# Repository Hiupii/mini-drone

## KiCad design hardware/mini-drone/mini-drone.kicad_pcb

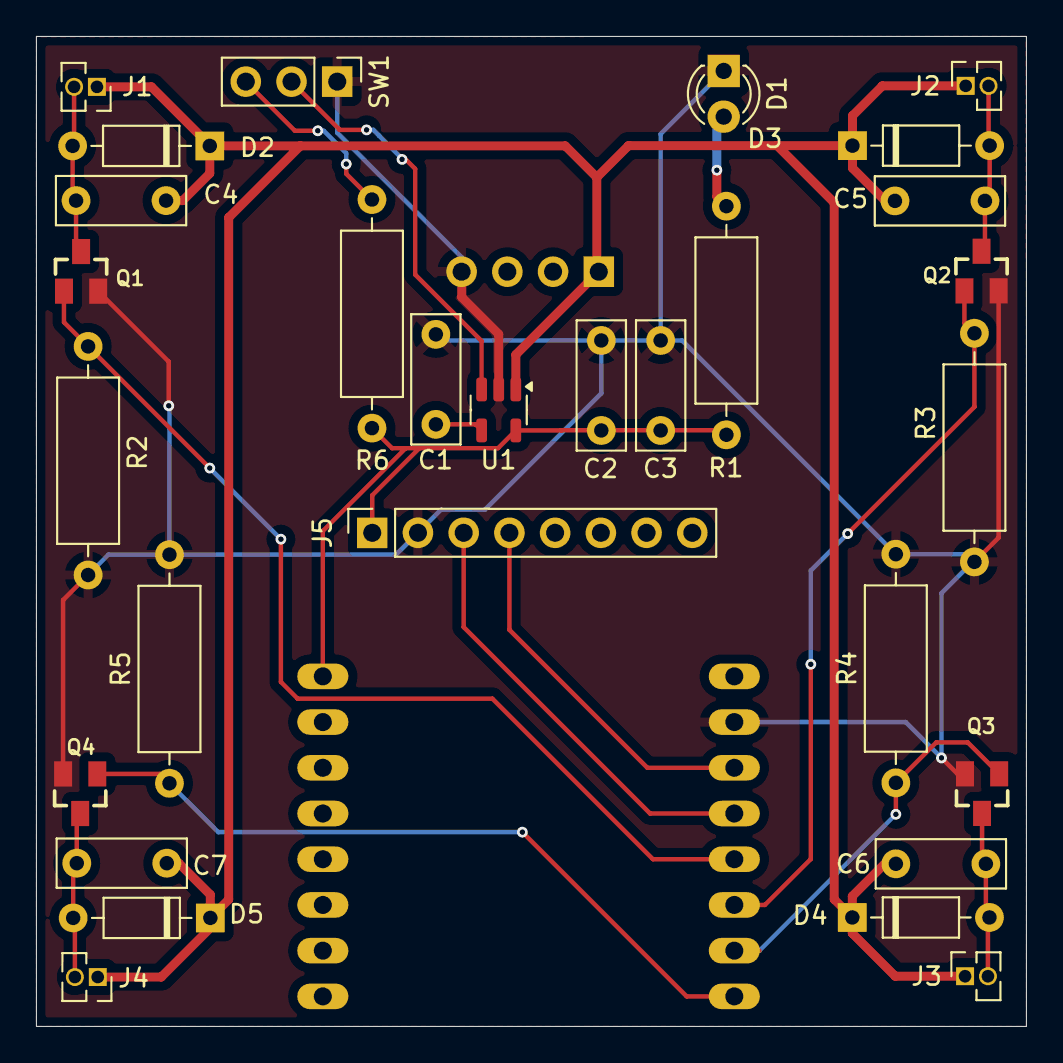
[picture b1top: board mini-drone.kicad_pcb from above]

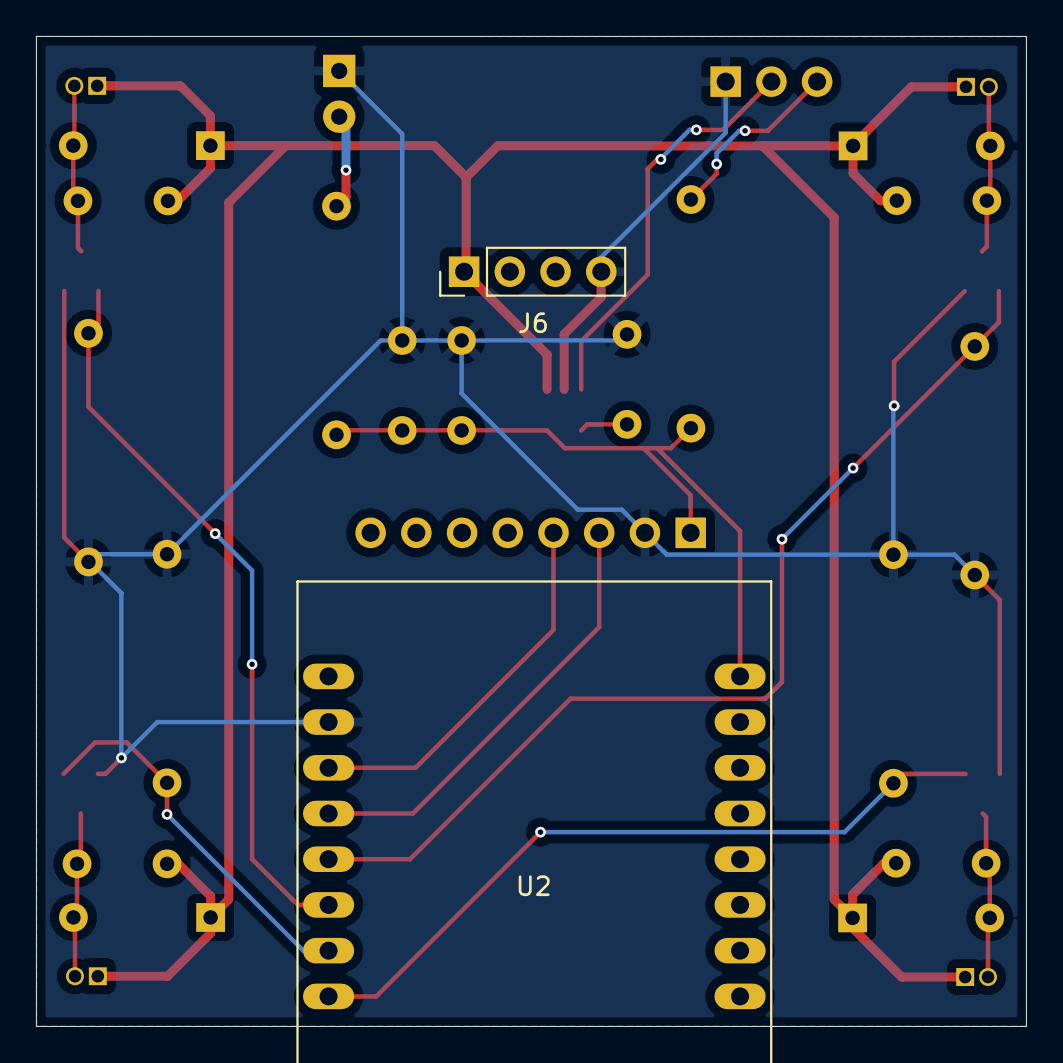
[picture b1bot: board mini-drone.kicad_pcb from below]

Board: 2 copper layers, 55.0 x 55.0 mm, 31 parts (2 on the bottom side), 17 nets.

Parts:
C1: 470pF; C_Disc_D7.0mm_W2.5mm_P5.00mm
C2: 2.2uF; C_Disc_D7.0mm_W2.5mm_P5.00mm
C3: 10uF; C_Disc_D7.0mm_W2.5mm_P5.00mm
C4, C5, C6, C7: 1uF; C_Disc_D7.0mm_W2.5mm_P5.00mm
D1: LED; LED_D3.0mm
D2, D3, D4, D5: 1N4148; D_DO-35_SOD27_P7.62mm_Horizontal
J1, J2, J3, J4: Conn_01x02_Socket; PinSocket_1x02_P1.27mm_Vertical
J5: Conn_01x08_Socket; PinSocket_1x08_P2.54mm_Vertical
J6: Conn_01x04_Pin; PinHeader_1x04_P2.54mm_Vertical
Q1, Q2, Q3, Q4: SI2302; SOT23
R1: 470R; R_Axial_DIN0309_L9.0mm_D3.2mm_P12.70mm_Horizontal
R2, R3, R4, R5: 10k; R_Axial_DIN0309_L9.0mm_D3.2mm_P12.70mm_Horizontal
R6: 100K; R_Axial_DIN0309_L9.0mm_D3.2mm_P12.70mm_Horizontal
SW1: K3-1280S-F1; PinHeader_1x03_P2.54mm_Vertical
U1: MIC5219-3.3YM5; SOT-23-5
U2: ESP32-CAM

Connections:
+3.3V: C2.1, C3.1, J5.1, R1.1, R6.1, U1.5 (OUT), U2.P$16 (3V3)
/+OUT: C4.1, C5.1, C6.1, C7.1, D2.1 (K), D3.1 (K), D4.1 (K), D5.1 (K), J1.1, J2.1, J3.1, J4.1, J6.1, U1.1 (IN)
/LDO_H: R6.2, SW1.3 (C)
/MOT_1: Q1.1, R2.1, U2.P$5 (IO15)
/MOT_2: Q2.1, R3.1, U2.P$6 (IO14)
/MOT_3: Q3.1, R4.1, U2.P$7 (IO2)
/MOT_4: Q4.1, R5.1, U2.P$8 (IO4)
/MPU_SCL: J5.3, U2.P$4 (IO13)
/MPU_SDA: J5.4, U2.P$3 (IO12)
GND: C1.2, C2.2, C3.2, D1.1 (K), J5.2, J6.4, Q1.2, Q2.2, Q3.2, Q4.2, R2.2, R3.2, R4.2, R5.2, SW1.1 (A), U1.2 (GND), U2.P$2 (GND)
LDO_EN: SW1.2 (B), U1.3 (EN)
unnamed: D1.2 (A), R1.2
unnamed: C4.2, D2.2 (A), J1.2, Q1.3
unnamed: C5.2, D3.2 (A), J2.2, Q2.3
unnamed: C6.2, D4.2 (A), J3.2, Q3.3
unnamed: C7.2, D5.2 (A), J4.2, Q4.3
unnamed: C1.1, U1.4 (BP)

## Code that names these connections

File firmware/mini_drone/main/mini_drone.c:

#include <stdio.h>
#include "freertos/FreeRTOS.h"
#include "freertos/task.h"
#include "esp_log.h"
#include "esp_event.h"
#include "esp_system.h"
#include "PID.h"
#include "mpu6050.h"
#include "driver/ledc.h"
#include "math.h"

/*----------mpu6050 var----------*/
#define MPU_ADDR (0x68)

#define CONFIG_SDA_GPIO GPIO_NUM_13
#define CONFIG_SCL_GPIO GPIO_NUM_12

static const char *MPU_TAG = "mpu6050_log";

static mpu6050_acceleration_t accel = { 0 };
static mpu6050_rotation_t rotation = { 0 };

static float input_pitch = 0.0f;
static float input_roll = 0.0f;
static float g = 9.81f;

/*----------pid var----------*/

struct pid_controller pitch_control;
pid_t pitch_pid;

struct pid_controller roll_control;
pid_t roll_pid;

float Kp = 3.55;   // Proportional param
float Ki = 0.005;   // Integral param
float Kd = 2.05;   // Derivative param

static float output_pitch = 0.0f;
static float output_roll = 0.0f;
static float setpoint_pitch = 0.0f;
static float setpoint_roll = 0.0f;


/*----------motor var----------*/
#define MOT_1 GPIO_NUM_14
#define MOT_2 GPIO_NUM_15
#define MOT_3 GPIO_NUM_2
#define MOT_4 GPIO_NUM_4

int base_throttle = 4915;
int motor1_pwm = 0;
int motor2_pwm = 0;
int motor3_pwm = 0;
int motor4_pwm = 0;

int constrain(int value, int min_value, int max_value);

void mpu6050_task(void *pvParameters)
{
    mpu6050_dev_t dev = { 0 };

    ESP_ERROR_CHECK(mpu6050_init_desc(&dev, MPU_ADDR, 0, CONFIG_SDA_GPIO, CONFIG_SCL_GPIO));

    while (1)
    {
        esp_err_t res = i2c_dev_probe(&dev.i2c_dev, I2C_DEV_WRITE);
        if (res == ESP_OK)
        {
            ESP_LOGI(MPU_TAG, "Found MPU60x0 device");
            break;
        }
        ESP_LOGE(MPU_TAG, "MPU60x0 not found");
        vTaskDelay(pdMS_TO_TICKS(1000));
    }

    ESP_ERROR_CHECK(mpu6050_init(&dev));

    ESP_LOGI(MPU_TAG, "Accel range: %d", dev.ranges.accel);
    ESP_LOGI(MPU_TAG, "Gyro range:  %d", dev.ranges.gyro);

    while (1)
    {
        ESP_ERROR_CHECK(mpu6050_get_motion(&dev, &accel, &rotation));
        input_pitch = asinf(accel.x * g / g) * 180 / M_PI;
        input_roll = atan2(accel.y, accel.z) * 180 / M_PI;
        ESP_LOGI(MPU_TAG, "Pitch: %f", input_pitch);
        ESP_LOGI(MPU_TAG, "Roll : %f", input_roll);

        pid_compute(pitch_pid);
        pid_compute(roll_pid);

        // ESP_LOGI(PID_TAG, "Input Pitch: %f, Output Pitch: %f", input_pitch, output_pitch);
        // ESP_LOGI(PID_TAG, "Input Roll : %f, Output Roll : %f", input_roll, output_roll);

        motor1_pwm = base_throttle + output_pitch - output_roll;
        motor2_pwm = base_throttle + output_pitch + output_roll;
        motor3_pwm = base_throttle - output_pitch + output_roll;
        motor4_pwm = base_throttle - output_pitch - output_roll;

        motor1_pwm = constrain(motor1_pwm, 0, 8191);  // 13-bit PWM max value is 8191
        motor2_pwm = constrain(motor2_pwm, 0, 8191);
        motor3_pwm = constrain(motor3_pwm, 0, 8191);
        motor4_pwm = constrain(motor4_pwm, 0, 8191);

        // ESP_LOGI(PID_TAG, "mot1_pwm: %d", motor1_pwm-base_throttle);
        // ESP_LOGI(PID_TAG, "mot2_pwm: %d", motor2_pwm-base_throttle);
        // ESP_LOGI(PID_TAG, "mot3_pwm: %d", motor3_pwm-base_throttle);
        // ESP_LOGI(PID_TAG, "mot4_pwm: %d", motor4_pwm-base_throttle);

        ledc_set_duty(LEDC_HIGH_SPEED_MODE, LEDC_CHANNEL_0, motor1_pwm);
        ledc_set_duty(LEDC_HIGH_SPEED_MODE, LEDC_CHANNEL_1, motor2_pwm);
        ledc_set_duty(LEDC_HIGH_SPEED_MODE, LEDC_CHANNEL_2, motor3_pwm);
        ledc_set_duty(LEDC_HIGH_SPEED_MODE, LEDC_CHANNEL_3, motor4_pwm);
        ledc_update_duty(LEDC_HIGH_SPEED_MODE, LEDC_CHANNEL_0);
        ledc_update_duty(LEDC_HIGH_SPEED_MODE, LEDC_CHANNEL_1);
        ledc_update_duty(LEDC_HIGH_SPEED_MODE, LEDC_CHANNEL_2);
        ledc_update_duty(LEDC_HIGH_SPEED_MODE, LEDC_CHANNEL_3);

        vTaskDelay(pdMS_TO_TICKS(100));
    }
}

// Thiết lập PWM cho động cơ
void setup_pwm() {
    // Cấu hình PWM cho 4 động cơ
    ledc_timer_config_t ledc_timer = {
        .duty_resolution = LEDC_TIMER_13_BIT, // Độ phân giải PWM
        .freq_hz = 5000,                      // Tần số PWM
        .speed_mode = LEDC_HIGH_SPEED_MODE,   // Chế độ tốc độ cao
        .timer_num = LEDC_TIMER_0             // Sử dụng bộ timer 0
    };
    ledc_timer_config(&ledc_timer);

    ledc_channel_config_t ledc_channel[4] = {
        {.channel    = LEDC_CHANNEL_0,
         .duty       = 0,
         .gpio_num   = MOT_1,          // Chân GPIO nối với động cơ 1
         .speed_mode = LEDC_HIGH_SPEED_MODE,
         .hpoint     = 0,
         .timer_sel  = LEDC_TIMER_0},

        {.channel    = LEDC_CHANNEL_1,
         .duty       = 0,
         .gpio_num   = MOT_2,          // Chân GPIO nối với động cơ 2
         .speed_mode = LEDC_HIGH_SPEED_MODE,
         .hpoint     = 0,
         .timer_sel  = LEDC_TIMER_0},

        {.channel    = LEDC_CHANNEL_2,
         .duty       = 0,
         .gpio_num   = MOT_3,          // Chân GPIO nối với động cơ 3
         .speed_mode = LEDC_HIGH_SPEED_MODE,
         .hpoint     = 0,
         .timer_sel  = LEDC_TIMER_0},

        {.channel    = LEDC_CHANNEL_3,
         .duty       = 0,
         .gpio_num   = MOT_4,          // Chân GPIO nối với động cơ 4
         .speed_mode = LEDC_HIGH_SPEED_MODE,
         .hpoint     = 0,
         .timer_sel  = LEDC_TIMER_0},
    };
    for (int i = 0; i < 4; i++) {
        ledc_channel_config(&ledc_channel[i]);
    }
}

void app_main()
{
    setup_pwm();

    ledc_set_duty(LEDC_HIGH_SPEED_MODE, LEDC_CHANNEL_0, base_throttle);
    ledc_set_duty(LEDC_HIGH_SPEED_MODE, LEDC_CHANNEL_1, base_throttle);
    ledc_set_duty(LEDC_HIGH_SPEED_MODE, LEDC_CHANNEL_2, base_throttle);
    ledc_set_duty(LEDC_HIGH_SPEED_MODE, LEDC_CHANNEL_3, base_throttle);
    ledc_update_duty(LEDC_HIGH_SPEED_MODE, LEDC_CHANNEL_0);
    ledc_update_duty(LEDC_HIGH_SPEED_MODE, LEDC_CHANNEL_1);
    ledc_update_duty(LEDC_HIGH_SPEED_MODE, LEDC_CHANNEL_2);
    ledc_update_duty(LEDC_HIGH_SPEED_MODE, LEDC_CHANNEL_3);

    // task
    ESP_ERROR_CHECK(i2cdev_init());

    pitch_pid = pid_create(&pitch_control, &input_pitch, &output_pitch, &setpoint_pitch, Kd, Ki, Kp);
    roll_pid = pid_create(&roll_control, &input_roll, &output_roll, &setpoint_roll, Kp, Ki, Kd);

    pid_limits(pitch_pid, -8191, 8191);
    pid_limits(roll_pid, -8191, 8191);

    pid_auto(pitch_pid);
    pid_auto(roll_pid);

    xTaskCreate(mpu6050_task, "mpu6050_test", configMINIMAL_STACK_SIZE * 6, NULL, 5, NULL);
}

int constrain(int value, int min_value, int max_value) {
    if (value < min_value) {
        return min_value;
    } else if (value > max_value) {
        return max_value;
    } else {
        return value;
    }
}

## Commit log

2024-09-01 pid algorithm added
2024-09-10 change gpio for esp32-cam, add pwm to motor
2024-09-18 balance function prototype
2024-09-18 complete PCB layout
2024-10-20 Change platform to Arduino
2024-11-04 Update drone controller
2024-12-24 Add Flask app into project
2024-12-29 firmware update rtos
2025-01-02 software:add api tracking image in resources
2025-01-03 Delete software/static/resources/058321d1724b59bf4d94b32bfdee0455ea073a01@xl.jpeg
    temp
